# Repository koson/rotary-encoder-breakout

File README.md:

rotary-encoder-breakout
=======================

0.925" x 0.925" breakout board for generic 12mm rotary encoder with switch.

Licenses
--------

Hardware design released under the [Creative Commons License Attribution-ShareAlike 3.0](http://creativecommons.org/licenses/by-sa/3.0/)

Encoder library for Arduino/Teensy released under MIT license 
 * http://www.pjrc.com/teensy/td_libs_Encoder.html
 * Copyright (c) 2011,2013 PJRC.COM, LLC - Paul Stoffregen <paul@pjrc.com>

Additional LEDfader example released to public domain by Thomas Price.

Version history
---------------

_RE01_

First version.

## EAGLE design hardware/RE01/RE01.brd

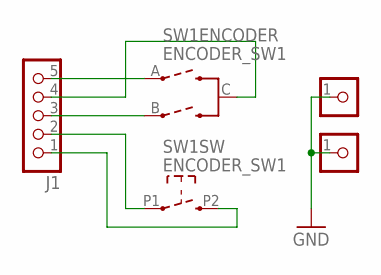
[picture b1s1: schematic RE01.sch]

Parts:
H1, H2: PROTO_VIAS_01X01
J1: CON_HEADER_1X05-PTH; M1X5
SW1: ENCODER_SW1; GENERIC_12MM_INCREMENTAL_ENCODER

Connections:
A: J1.5, SW1.A
B: J1.3, SW1.B
C: J1.4, SW1.C
GND: H1.1, H2.1
P1: J1.2, SW1.P1 (1)
P2: J1.1, SW1.P2 (2)

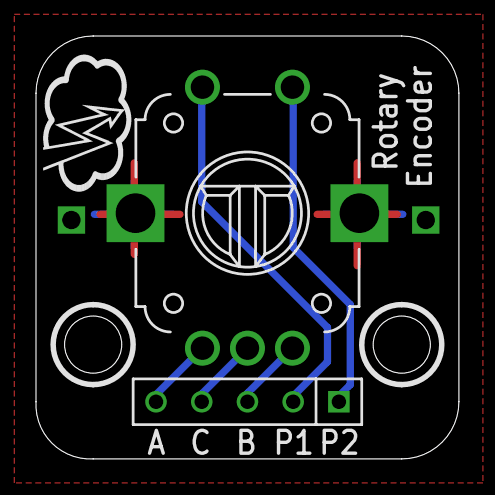
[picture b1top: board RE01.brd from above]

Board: 4 copper layers, 23.5 x 23.5 mm, 5 parts (1 on the bottom side), 6 nets.

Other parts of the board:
U$1: OSHW-LOGO-S

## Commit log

2013-12-03 RE01 Elecrow order
2013-12-24 Encoder library for Arduino

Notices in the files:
hardware/RE01/RE01.brd:
CC BY-SA 3.0
parts and their libraries:
SparkFun: Licensing: CC v3.0 Share-Alike You are welcome to use this library for commercial purposes.
